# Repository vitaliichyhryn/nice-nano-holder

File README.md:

# Holder PCB for nice!nano
Holder PCB for BastardKB TBK Mini

## WARNING
The PCBs have not been validated yet, they are not confirmed to be working!

## Features:
- Matrix pinout moved to low frequency pins
- SPI trackball connection moved to high frequency pins
- Removed unused connectors and pins
- Added PH 2.0 battery connector

## License 
This work is licensed under a Creative Commons Attribution-NonCommercial-ShareAlike 4.0 International License.

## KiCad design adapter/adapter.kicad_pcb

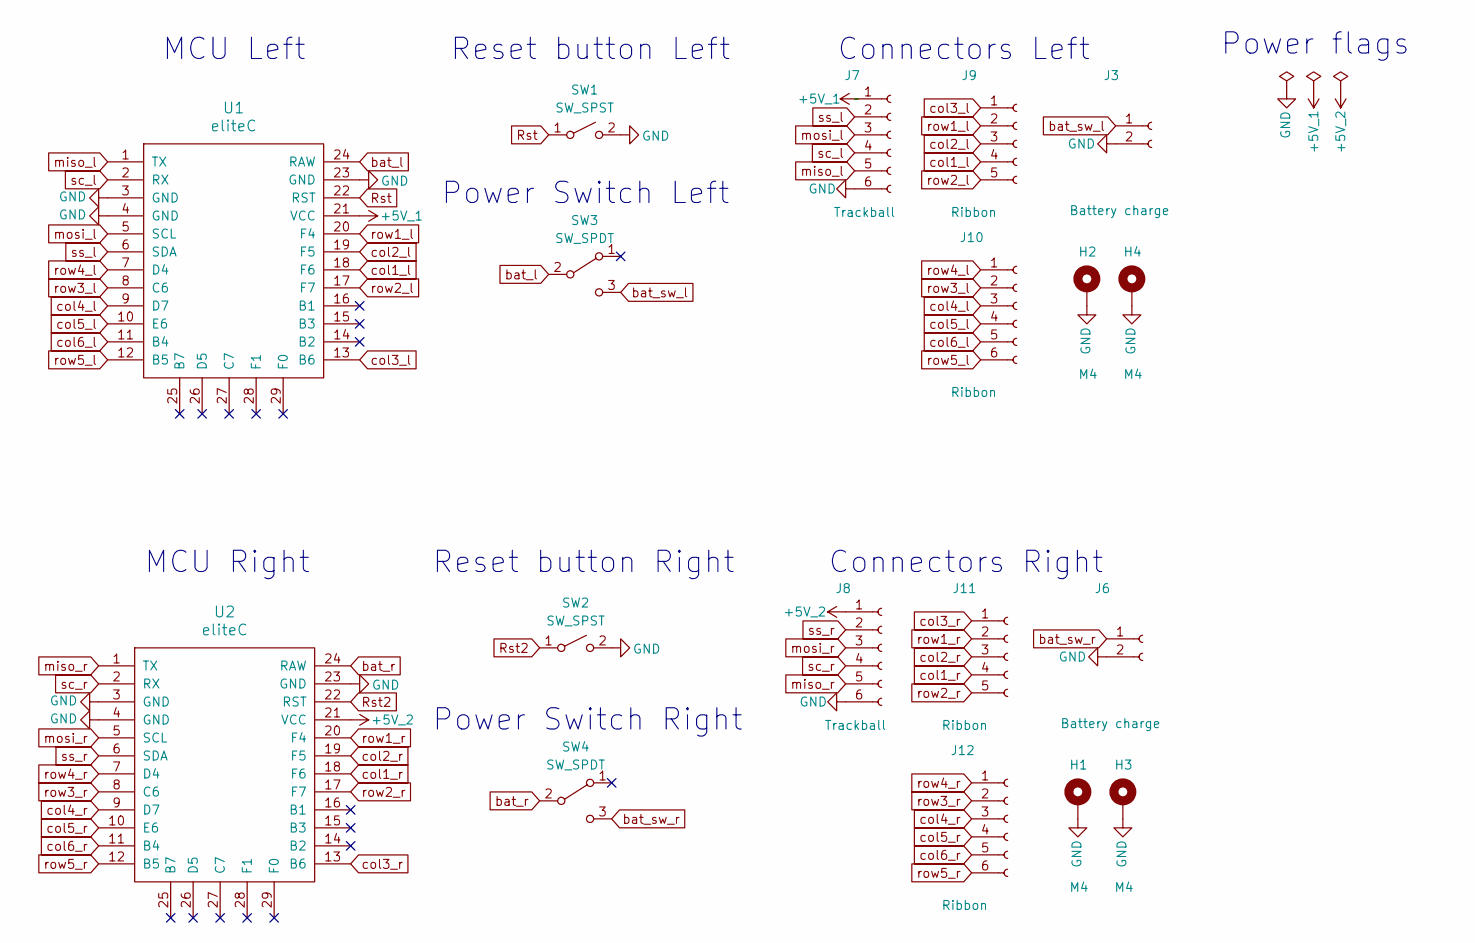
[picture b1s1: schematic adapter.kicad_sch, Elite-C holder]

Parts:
H1, H2, H3, H4: M4; MountingHole_4mm_Pad_thin
J3, J6: Battery charge; JST_PH_B2B-PH-K_1x02_P2.00mm_Vertical
J7, J8: Trackball; 6_PinHeader
J9, J11: Ribbon; 5_PinHeader
J10, J12: Ribbon; 6_PinHeader
SW1, SW2: SW_SPST; PushSwitch
SW3, SW4: SW_SPDT; SW_SPDT+H-MSK12C01_hor(7pin_SMD)
U1, U2: eliteC; Elite-C

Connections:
+5V_1: J7.1, U1.21 (VCC)
+5V_2: J8.1, U2.21 (VCC)
GND: H1.1, H2.1, H3.1, H4.1, J3.2, J6.2, J7.6, J8.6, SW1.2 (B), SW2.2 (B), U1.3 (GND), U1.4 (GND), U1.23 (GND), U2.3 (GND), U2.4 (GND), U2.23 (GND)
Rst: SW1.1 (A), U1.22 (RST)
Rst2: SW2.1 (A), U2.22 (RST)
bat_l: SW3.2 (B), U1.24 (RAW)
bat_r: SW4.2 (B), U2.24 (RAW)
bat_sw_l: J3.1, SW3.3 (C)
bat_sw_r: J6.1, SW4.3 (C)
col1_l: J9.4, U1.18 (F6)
col1_r: J11.4, U2.18 (F6)
col2_l: J9.3, U1.19 (F5)
col2_r: J11.3, U2.19 (F5)
col3_l: J9.1, U1.13 (B6)
col3_r: J11.1, U2.13 (B6)
col4_l: J10.3, U1.9 (D7)
col4_r: J12.3, U2.9 (D7)
col5_l: J10.4, U1.10 (E6)
col5_r: J12.4, U2.10 (E6)
col6_l: J10.5, U1.11 (B4)
col6_r: J12.5, U2.11 (B4)
miso_l: J7.5, U1.1 (TX)
miso_r: J8.5, U2.1 (TX)
mosi_l: J7.3, U1.5 (SCL)
mosi_r: J8.3, U2.5 (SCL)
row1_l: J9.2, U1.20 (F4)
row1_r: J11.2, U2.20 (F4)
row2_l: J9.5, U1.17 (F7)
row2_r: J11.5, U2.17 (F7)
row3_l: J10.2, U1.8 (C6)
row3_r: J12.2, U2.8 (C6)
row4_l: J10.1, U1.7 (D4)
row4_r: J12.1, U2.7 (D4)
row5_l: J10.6, U1.12 (B5)
row5_r: J12.6, U2.12 (B5)
sc_l: J7.4, U1.2 (RX)
sc_r: J8.4, U2.2 (RX)
ss_l: J7.2, U1.6 (SDA)
ss_r: J8.2, U2.6 (SDA)

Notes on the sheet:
Power Switch Right
Reset button Left
Power Switch Left
Connectors Left
Reset button Right
MCU Left
MCU Right
Power flags
Connectors Right

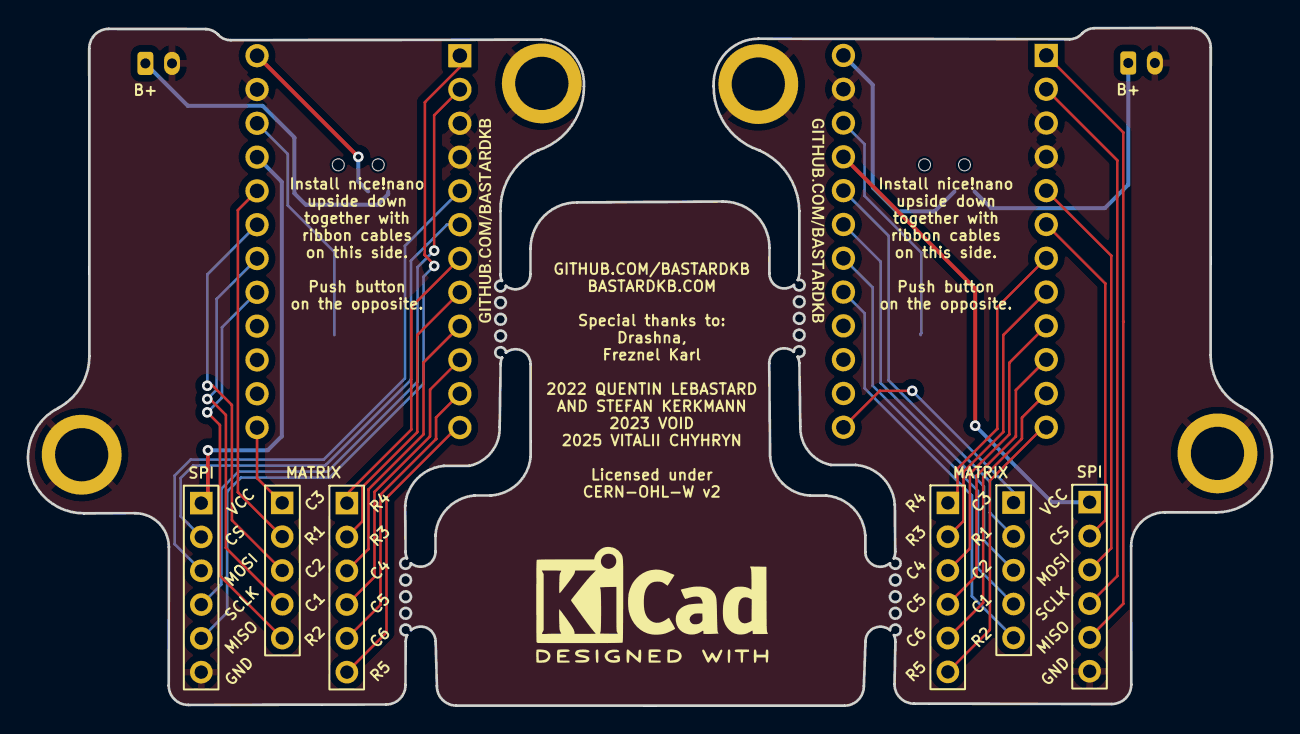
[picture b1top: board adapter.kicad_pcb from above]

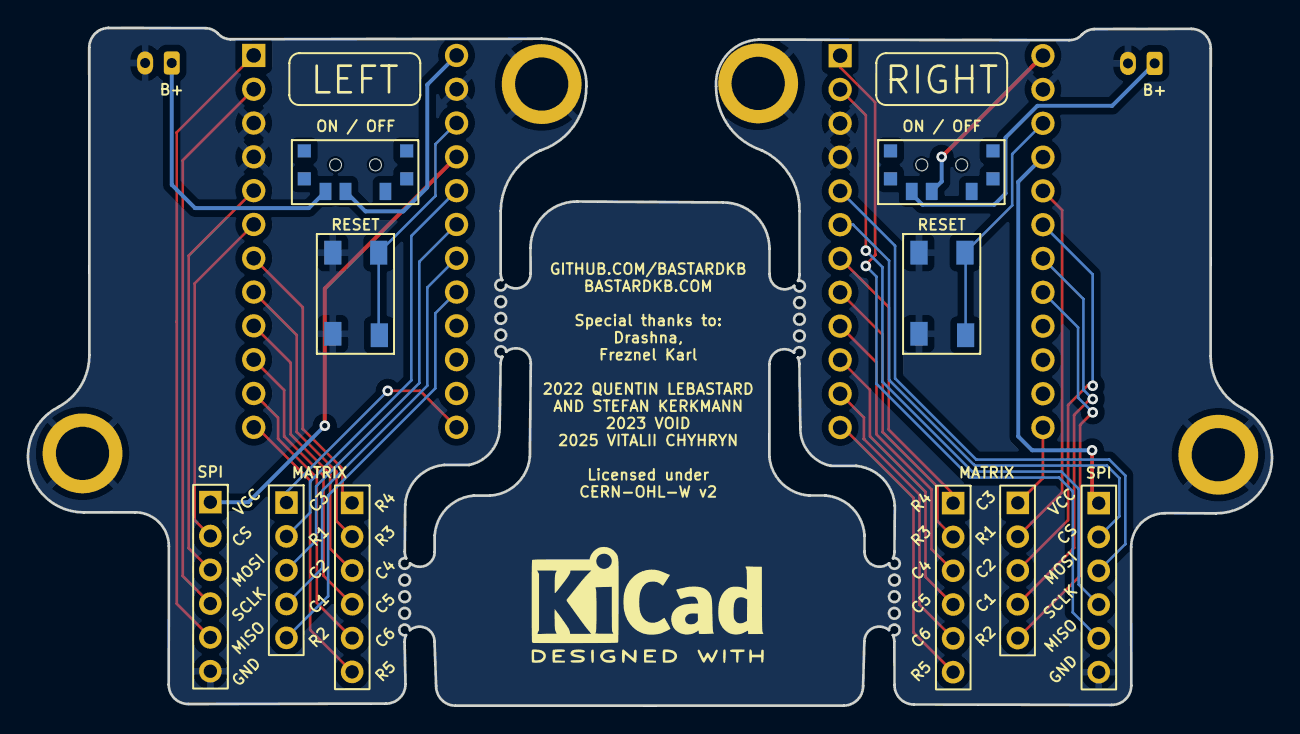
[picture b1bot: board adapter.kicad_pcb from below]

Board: 2 copper layers, 93.5 x 50.9 mm, 20 parts (6 on the bottom side), 39 nets.

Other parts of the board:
kibuzzard-61F01A92, kibuzzard-61F01A92#2: G***; kibuzzard-61F01A92

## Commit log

2023-05-12 updated design
    - swapped high frequency pins from matrix to spi
    - removed jacks and serial resistors
    - added ph2 battery headers
    - moved reset buttons
    - gerbers added to production dir
2023-06-15 updated schematic
    - updated schematic to reflect pcb changes
    - removed rgb, serial, swapped spi pinout, updated battery footprint
2025-06-27 Update project file
2025-06-28 Clean up courtyard and fabrication layers
2025-06-28 Revert to old board outlines
2025-06-28 Remove serial from schematic
2025-06-28 Move reset button and power switch
2025-06-28 Add screenshots of PCBs
2025-06-28 Update gerbers
2025-06-29 Move back the power switch and reset button
2025-06-29 Update gerber
2025-06-29 Update pics
2025-06-29 Realign one of the pins

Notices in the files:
adapter/adapter.kicad_pcb:
CERN-OHL-W v2
adapter/adapter.kicad_sch:
Licensed under CERN-OHL-W v2
